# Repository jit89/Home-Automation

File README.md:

### Home-Automation: Thinking Differently
With the emergence of the IOT [(Internet of Things)](https://en.wikipedia.org/wiki/Internet_of_things) , automation has become a part and parcel of our daily lives. Starting from lights and fans, people have started to automate almost everything around them. After software giants like Amazon and Google started providing cloud services, people came to use the free resources provided by them to store/log their data and manage them from a distance even without having direct physical contact with the devices.
After this was pretty well-exploited, people started combining the power of machine learning with the existing technology. With rapid improvement in hardware and GPU's becoming cheap, it has become quite easy for an individual to learn, test out and contribute to the advancement of machine learning. Powerful methods like use of [deep learning](https://en.wikipedia.org/wiki/Deep_learning) in visual image processing, natural langugage processing etc has made this existing technology even more smarter. Popular home assistants like Amazon [Alexa](https://developer.amazon.com/alexa) etc, by making their API's open sourced have encouraged development in home automation even more.
### Why re-invent the wheel then ?
You might ask, well a lot of people have spent years writing and perfecting their techniques, why not build our application atop them ? Why do we even need to think about something from scratch where we have already progressed so far ? The answer is very simple, in fact this the reason for which we took up this project. We couldn't agree well with the existing idea of automation. I know, there are some brilliant projects out there at [Instructables](https://www.instructables.com/), [Hackaday](https://hackaday.com/) and [Hackster](https://www.hackster.io/) etc where people have put a lot of effort making a very neat and appealing project and I appreciate their effort. But controlling lights, fans, switches and other power ports using bluetooth, WiFi and other technologies through a custom designed Android/iOS application may be excellent but they are over exploited already. Yeah, you can switch on your Television and washing machine, turn off the radio, feed your pet, monitor the weather while sitting on your couch while watching your favourite series on Netflix but this has already been done, right ? We are already living those days, but what if your TV knew when do you watch it mostly ? What if your lights and fans knew when to turn on and when not to so they could save the maximum power when you are not in in your room ? That is much better than controlling your lights, fans, television etc through a Bluetooth controlled Arduino or telling Alexa to switch it on/off for you. My point is, the devices which we use everyday should develop some kind of intelligence so that they can know when they are used mostly and thus turn themselves on during those hours without you, manually switching it on. This is exactly what we try to do here.
### The Idea
Keeping aside all big talks, our aim is simple, designing a system that learns to map user behaviour. Citing a small example here, Suppose, you live alone in small apartment with only three appliances in your house, two lights and a fan, lets call them **LIGHT 1**, **LIGHT 2** and **Fan**. Now, consider the following case:
* You wake up at 07:00 (7:00 AM) hours and do your daily chores.
* You leave for office at 08:00 Hours (8:00 AM).
* You return home at 19:00 Hours (7:00 PM).

You follow the above routine on most working days. After waking up (i.e is after 07:00) hrs and before leaving for your office at 08:00 hrs suppose you use light 1 and the fan. After returning from office, you use all three of the appliances. Since, you dont have many switches in the room, you don't have much room for exploring more options, as a result you follow a similar routine everyday.
If we use our prototype here, what our system will do is, it will learn when and how much you used the appliance and from the very next day try to follow the same routine as followed by you the previous days. This wont be done from the start, after you install the prototype it will observe you for a day which we call as the **observation period**.
### The Brief Technicalities
Its time for us now, to dive into brief technical details. Our application is actually a room automation module which is used to automate your room, this module provides a drop in replacement for your switchboard so that you do not need to touch your switch board again. The form factor of the module will be so made that it retro-fits behind your switchboard. You can then control the functionalities of the physical switches of your switchboard through a smartphone application, just like any other home automation device. But Wait! There is much more to it. Apart, from controlling them at your own will from the smartphone application you can very well control them by the physical switches if you like. We are not taking away your rights over your switchboard! This, comes in handy if the module or the smartphone application goes haywire, you can anyway use your switches without any worry. Wait, There is even more! Like I said before, the system takes into account your choices of switching appliances on and off both through the physical switches and through the smartphone device. After it has gathered enough data and after you allow it to, it will predict what appliance you might switch on at a certain time of the day and switches on that appliance. Its like, you come home everyday at 19:00 hrs (7:00 PM) and switch on the fan hanging over your sofa, but one day you find out as soon as you come home at or after 19:00 hrs (7:00 PM) the fan switches on by itself!
### Some Additional features
1. A lot of features have been mentioned already but what I would like to add here is, such a system works by mapping user action throughout the day and reproducing them later. Well, you might say, OK, I agree that someone can maintain some coherence in his/her routine for a day or two, but someone cannot follow the same pattern for days after days, for Heavens's sake we are not machines! We, too thought about this, how you will deal with your home appliances tomorrow cannot be exactly predicted by observing how you dealt with them today, we can only get a rough idea. If you observe someone for a day, the conclusion you will reach will be an abstract idea, like:
  > "Ohh, so he likes to leave all lights on during the night",

  or maybe something like this:

  > "Ohh, he switches on more tubelights in the night than in the day",

  or, more likely something like this:

  > "I bet, he uses only half of the appliances he has, in his house".

These are all rough estimates which might be true for a day or two but cannot be guaranteed over a longer period of time. So, How do you get make good estimtes ? Well you keep a watch more frequently and try to understand how much the behaviour of the user differs each day and update your observation accordingly. Our system exactly does that, it keeps a note of your usage behaviour very frequently and tries to draw and inference from that, after a day is over it updates its observations.

2. Since, the system follows the user's behaviour and updates itself as soon as the user's behaviour changes, the device isnt affected by the change of seasons, timezones, geographic locations etc. It all depends on how you use it. 
### How is it being done ?
Before starting, let me tell you quite frankly, that the idea is still in the developmental stage and a lot of community help is required to further polish it. Only a working prototype is being developed here. Our goal is to make a small, easy-to-interface  embedded module made from commonly available parts which will be having enough intelligence to provide descisions based on observing a particular user.
* Lets, talk about the hardware first, We are using [ESP8266-ESP12](https://www.elecrow.com/download/ESP-12S_User_Manual.pdf) [Wemos D1 Mini](https://wiki.wemos.cc/products:retired:d1_mini_v2.2.0) here. 
  * Three pins are configured as outputs for controlling a relay through a BJT (Bipolar Junction Transistor) or probably a MOSFET in the future, for switching high voltage appliances. 
  * A [PIR (Passive Infrared Sensor)](https://cdn-learn.adafruit.com/downloads/pdf/pir-passive-infrared-proximity-motion-sensor.pdf) is used to detect the occupancy of a person in the room, the output of the PIR sensor is fed to a pin configured as input. 
  * For storing the data permanently an i2c [FRAM](http://www.cypress.com/file/136491/download) will be used, FRAM being chosen particularly because of its fast write time and very large read/write cycles in comparison to any eeprom or flash memory.
* The software used to program the ESP is micropython. They are seriously brilliant guys who made micropython possible. I would suggest you to take a look at ther [repository](https://github.com/micropython/micropython) for more information. The software will manage all the afore mentioned hardware. A small single neural network with a single hidden layer will be employed to predict the appliance which needs to be turned on/off, given a particular time and a state (i.e the person is in the house or not). Please note that we are not doing a time series prediction anyway, we are not trying to model the user's behaviour as time series beacuse such a series would be very stochastic, it would more and more difficult to find a pattern in the user's behaviour if the observations are taken for a very long period of time. Our model is based on the assumption that the chance of the user,  using our system, to repeat his/her routine is maximum the very next day, i.e if today is Tuesday, there is more probability of the user to follow a similar routine for Wednesday, but would be very difficult to say in advance that the user will follow a similar routine on Saturday or Sunday. Obviously, hard coding such an assumption is a very naive choice indeed because there can be many cases which might simply outrun the assumption, but for the sake of simplicity such an assumption is made. But some other methods are also employed to alleviate the issue. 
* A smartphone application is being developed too for user access through a smartphone.
* A server side script which the ESP8266 and the smartphone application will connect to enable the user to acces the home appliances from anywhere in the world. The server side script will be written in CPython. We intend to buy a domain for this purpose.

### The occupancy detection algorithm
Since, we have already talked about the hardware and the software separately, its time we combine both of them to state an algorithm followed by the system. A little note here, we are using PIR to detect if a person is present in the room, once the person gets out of his/her room we switch off the appliances present in the room when the user gets back inside, the appliances switch on. But do all of them switch on ? No, only those appliances switch on, which have been switched on by the user in the previous days when the system was observing the user during the **observation period**. This essentially means, once you come inside of your room you need not switch on your home appliances yourself, the system does it for you, it remebers what appliances you had switched on during that time in the previous days, and switches on that appliance which has a high probability of being switched on by you during that time.
Now we can discuss about the occupancy detection algorithm, our idea is inspired from [this](https://www.researchgate.net/publication/308007740_Predicting_room_occupancy_with_a_single_passive_infrared_PIR_sensor_through_behavior_extraction) paper. The paper discusses sophisticated filtering and detection methods none of which are employed here, still its worth a read if you are into mathematics and love reading articles related to applied machine learning. The only part of our idea taken from the paper is that we are using only a single PIR. What we previously did was to keep two PIR's kept at a distance from each other in a fashion that is described in the left portion of the picture below:
    
    Our earlier layout                                  |                      PIR Filed of Vision       
    --------------------------------                    |                   -
          ---                                           |                 -
      PIR 1  |--                                        |               -
             |  |                                       |             -
             |--                                        |           --
          ---                                           |  ---    -    --
                                                        |     |--        --
    ----------------------------------                  | PIR |  |         -    120*
                                                        |     |--          -
    ----------------------------------                  |  ---    -       --
          ---                                           |           -   --
      PIR 2  |--                                        |             -
             |  |                                       |                -
             |--                                        |                   -
          ---                                           |                     -
    ----------------------------------                  |  

So, whenever someone crossed PIR 1, the output pin of the PIR 1 became high, and then after he crossed PIR 2, its output became high, we connected the output of the two PIR's to an Arduino and enabled both the arduino pins to fire interrupts whenever the state of the pin changed from low to high. Inside the interrupt service routine (ISR), which is the section of the code that gets executed during an interrupt occurs, we stored a timestamp. Now, suppose, when the person crosses PIR 1 we store the time stamp in a variable named **t1**, now when he crosses the PIR 2, we store the timestamp in a variable caleed **t2**. Now, if t2 is greater than t1, it means the PIR 1 fired before the PIR 2 and the person crossed PIR 1 first, we classified this movement as entry, if the opposite happened i.e if t1 was greater than t2, that is the person approached PIR 2 first and then PIR 1, we classified it as an exit. The method is simple enough but has many drawbacks like you have to cross the two PIR's linearly, also the field of vision of the PIR's are 120 degrees as drawn on the right side, so placing two PIR's side by side will cause their field of visions to overlap and it may often happen that the two PIR's fire together, to avoid that, we used a cylindrical enclosure to cover the PIR's partially, so that their field of vision's are forcibly narrowed, this wasn't a good practice and reduced the efficiency of PIR sensors and sometimes leading them to not fire at all.

After this, we came to the idea of using a single PIR after reading that research paper which I talked about earlier. We still connect the output of the PIR to our ESP and enable the pin to detect a rising edge. What we only dont do now is use another PIR, we let the single PIR fire freely on its own. If I haven't already talked about the delay in the PIRs, I'm going to talk about it now, if you have used a PIR before, then you might be knowing that after the PIR output pin has become high it stays high for a certain amount of time. While the PIR output is high it caanot detect any motion during that period. So, this is the minimum amount of time every PIR will wait before being available to take another reading. The delay varies across PIRs and I have rarely found two PIR sensors having the exact same amount of delay. The delay can be increased as well using the preset given in the PIR sensor board but for our use we keep it at its minimum. 
What we do now is, **sample the PIR output pin after every 5 seconds**, we define a quantity called activity which sees how many times we get a HIGH output from the PIR during a given span of time, here, the span being 1 hour. The PIR will fire only when a person moves inside the room. Thus if the person becomes motionless the PIR won't output a HIGH, so counting the HIGH states sampled from the PIR means to indirectly measure how much the person makes movement during his entire stay inside the room. But we are not just counting the number of HIGH outputs from the PIR and dividing it by 3600 seconds to get an average rate of HIGH fires or activity of the person. Why ? Because averaging out is a good solution to get a rough measure of the user activity inside the room but vital information like the minimum rate and the maximum rate during the person's stay in his room in an hour cannot be found out from the average. So, we keep track of the changes in the activity variable and keep two other variables for storing the maximum and the minimum activity during an hour of observation.

We will try to follow the below mentioned tree:

    ----root
        |----Hardware
                |----Schematics, datasheet and pcb design files
        |----Micropython
                |----Micropython code for the Esp
        |----Server
                |----Server side scripts
        |----Smartphone_Application
                |----All documentation related to the smartphone application

### Support
We would appreciate any help provided from your side in designing and developing this idea. We also welcome all kinds of comments and suggestions provided to us.

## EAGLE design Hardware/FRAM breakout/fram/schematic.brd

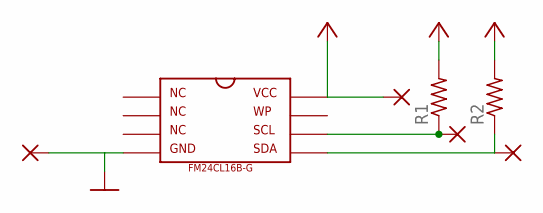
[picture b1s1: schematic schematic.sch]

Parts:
GND: SMD2; SMD1,27-2,54
R1, R2: R-US_M0805; M0805
SCL: SMD2; SMD1,27-2,54
SDA: SMD2; SMD1,27-2,54
U$1: FM24CL16B-G
VCC: SMD2; SMD1,27-2,54

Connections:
+3V3: R1.2, R2.2, U$1.8, VCC.1
GND: GND.1, U$1.4
unnamed: R1.1, SCL.1, U$1.6
unnamed: R2.1, SDA.1, U$1.5

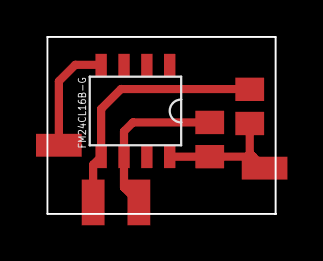
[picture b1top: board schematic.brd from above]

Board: 2 copper layers, 12.7 x 9.8 mm, 7 parts (0 on the bottom side), 4 nets.

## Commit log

2018-04-13 Added README.md
2018-04-13 Create Micropython
2018-04-13 Added Micropython directory
2018-04-13 Added server directory
2018-04-13 Added Smartphone_application directory
2018-04-13 Added Hardware directory
2018-04-14 Update README.md
    corrected hardware links
2018-04-16 Create Android app
2018-04-16 Added utils.py to micropython
2018-04-17 Added android app
2018-04-17 Added appliance and utils
2018-04-17 Added appliance and utils and main
2018-04-17 updated appliance.py
2018-04-17 Updated utils.py
2018-04-18 Buttons for different rooms Added
2018-04-18 room Button Funcitionally added
2018-04-20 new file: Hardware/FRAM breakout/fram/eagle.epf new file: Hardware/FRAM breakout/fram/gerber/mask.ps new file: Hardware/FRAM breakout/fram/gerber/solder.ps new file: Hardware/FRAM breakout/fram/outpu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
2018-04-20 FRAM breakout added
2018-04-20 FM24CL16B-G library updated
2018-04-20 renamed: Hardware/FRAM breakout/FM24CL16B-G eagle library/FM24CL16B-G_fram.lbr -> Hardware/Peripherals/FRAM breakout/FM24CL16B-G eagle library/FM24CL16B-G_fram.lbr renamed: Hardware/FRAM breakout/fra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
2018-04-20 Updated main.py
2018-04-20 navigation Drawer added and two different versions released
2018-04-20 updated class GPIO(object)
2018-04-20 hardware reference added
2018-04-20 Updated appliance.py, main.py
2018-04-20 updated rtc_init in utils.py
2018-04-21 Added saving/loading to FRAM as class methods
2018-04-22 UI fixed for most screen sizes
2018-04-22 UI optimised and UI support for almost all screen
2018-04-22 schematic added
2018-04-22 schematic updated
2018-04-22 Readme file added
2018-04-22 Basic splash screen on startup added
2018-04-22 ScreenShots added
2018-04-23 Login Screen added and credentials saved in sharedpreferences
2018-04-24 Info Activity created and nav drawer item logo added
2018-04-24 block diagrams updated
2018-04-24 Create LICENSE
2018-07-04 data fetching added
2018-07-05 using volley instead of asynctask for http request. screen on start fixed
2018-08-12 minor database updation added
